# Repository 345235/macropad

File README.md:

# macropad
This is a macropad that i build for stardance. It has 4 cherry switches a 128x32 oled-screen

# Features:

I2C OlED-Displaymodul SSD1306 Driverchip 
  
4 cherry switches 
 
seeedouino xiao

#
# CAD

#

# PCB

Here's my PCB! It was made in KiCad.

#

# Materials: 

Abs red 

Abs black

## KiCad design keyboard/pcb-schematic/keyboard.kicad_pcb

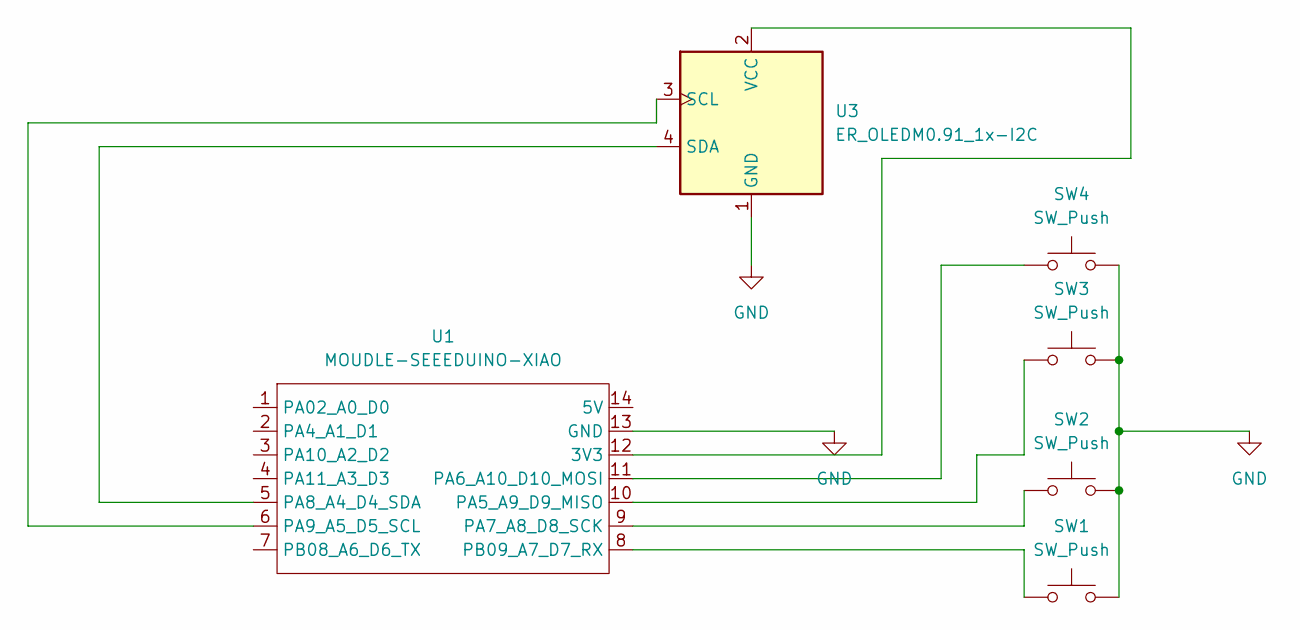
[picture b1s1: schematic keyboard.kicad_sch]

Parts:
SW1, SW2, SW3, SW4: SW_Push; SW_Cherry_MX_1.00u_PCB
U1: MOUDLE-SEEEDUINO-XIAO; XIAO-Generic-Hybrid-14P-2.54-21X17.8MM
U3: ER_OLEDM0.91_1x-I2C

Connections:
GND: SW1.2, SW2.2, SW3.2, SW4.2, U1.13 (GND), U3.1 (GND)
unnamed: U1.12 (3V3), U3.2 (VCC)
unnamed: SW3.1, U1.10 (PA5_A9_D9_MISO)
unnamed: SW4.1, U1.11 (PA6_A10_D10_MOSI)
unnamed: SW2.1, U1.9 (PA7_A8_D8_SCK)
unnamed: U1.5 (PA8_A4_D4_SDA), U3.4 (SDA)
unnamed: U1.6 (PA9_A5_D5_SCL), U3.3 (SCL)
unnamed: SW1.1, U1.8 (PB09_A7_D7_RX)

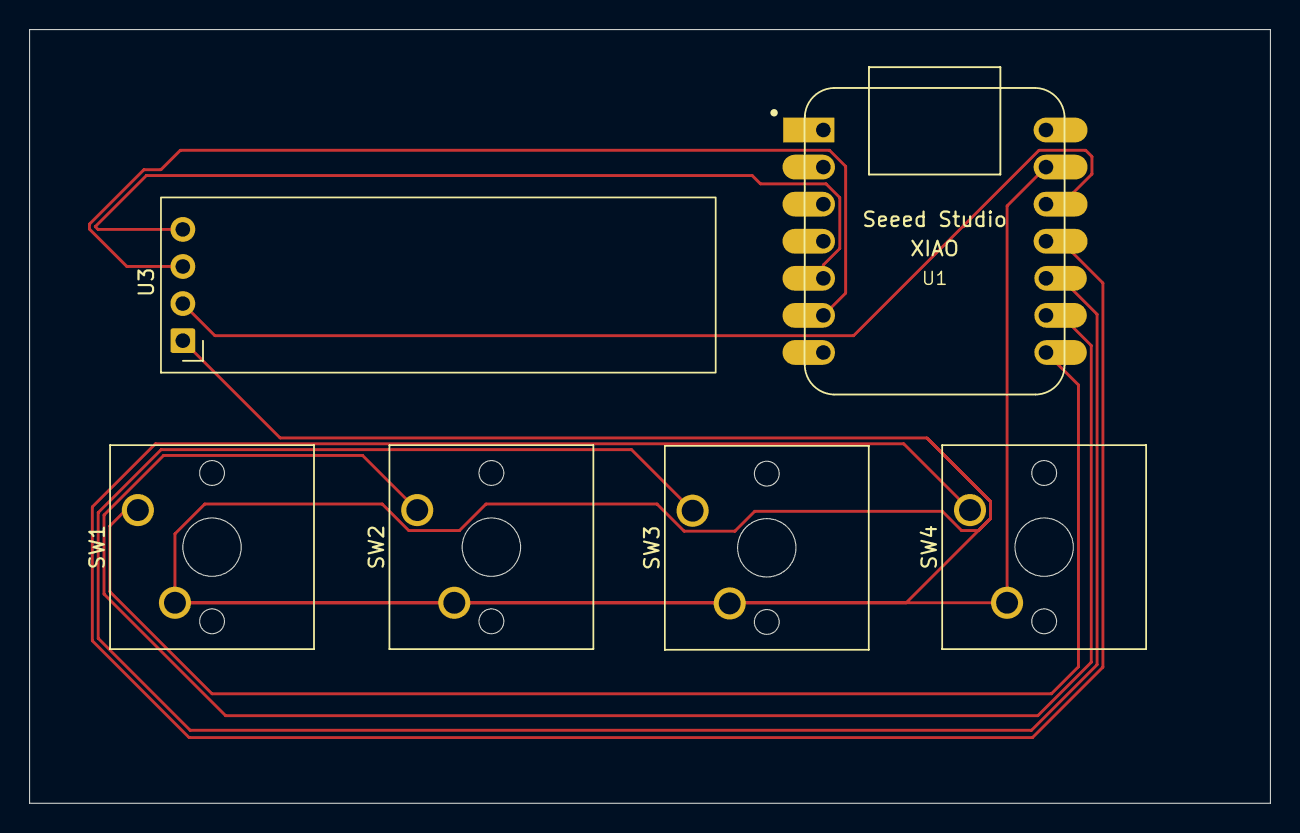
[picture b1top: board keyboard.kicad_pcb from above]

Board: 2 copper layers, 85.0 x 53.0 mm, 6 parts (0 on the bottom side), 8 nets.
